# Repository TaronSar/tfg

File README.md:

# ProtoNet UAV — local few-shot identification prototype

Minimal local prototype of the TFG pipeline: MobileNetV3-Small -> 576 -> Linear ->
LayerNorm -> 128-dim L2-normalized embeddings, prototypical episodic training,
enrollment to `gallery.npy`, identification by cosine similarity. No Embention
infrastructure required — runs on a single PC (CUDA or CPU).

## Setup

```bash
python -m venv .venv && source .venv/bin/activate   # or conda
pip install -r requirements.txt
```

## Data layout

One folder per **physical airframe / distinct model**, split by identity
(an identity must never appear in both splits):

```
data/
  train/
    identity_A/ img001.jpg ...
    identity_B/ ...
  val/
    identity_X/ ...
```

Guideline: >=10 train identities and >=5 val identities, >=10 images each, to
see meaningful learning. Crops of the object (detector-style) work best, but
full photos are fine for a first smoke test.

## Test sequence

**0. Zero-shot sanity check (no training).** The ImageNet-pretrained encoder
already produces usable embeddings:

```bash
python -m src.enroll --images data/val/identity_X_subset5 --out gallery.npy
python -m src.identify --gallery gallery.npy --images data/val/identity_X_rest
python -m src.identify --gallery gallery.npy --images data/val/identity_Y   # impostor
```

If genuine scores already sit above impostor scores, the metric-learning
premise holds before you train anything.

**1. Train:**

```bash
python -m src.train --data_root ./data --epochs 30 \
    --n_way 5 --k_shot 5 --q_query 5 --degrade_p 0.5
```

`--degrade_p 0.5` randomly degrades training images to the 46–143 px
operational envelope (downscale + blur + upscale). Set `0` to disable —
comparing both runs is your first Q3 data point.

**2. Open-set evaluation (the number that matters):**

```bash
python -m src.eval_openset --checkpoint checkpoints/best.pth \
    --data_root ./data --k_shot 5 --agg mean
python -m src.eval_openset --checkpoint checkpoints/best.pth \
    --data_root ./data --k_shot 5 --agg attention   # Approach 2
```

Reports ROC-AUC (target vs impostor) and TPR at FPR 1/5/10%. Run with
`--checkpoint` omitted first to get the zero-shot baseline; training should
beat it clearly. Sweep `--k_shot 1 3 5 10` for an early Q1 curve.

**3. Manual enrollment demo (what the client-side app will do):**

```bash
python -m src.enroll --checkpoint checkpoints/best.pth \
    --images photos_of_target/ --out gallery.npy
python -m src.identify --checkpoint checkpoints/best.pth \
    --gallery gallery.npy --images query_crops/ --agg attention --threshold 0.6
```

## Distance metric (Snell et al. 2017)

The default metric is **squared Euclidean** (`--metric euclidean`), not cosine.
Squared Euclidean is a Bregman divergence, which is the property that makes the
class mean the optimal prototype. Cosine is kept as `--metric cosine` for the
ablation.

Subtlety specific to this project: the encoder L2-normalizes embeddings by
default (required by the gallery/threshold/privacy design). On the unit sphere,
squared Euclidean and cosine are monotonically equivalent, so the Bregman
justification is satisfied trivially. To reproduce the paper's *unnormalized*
Euclidean setting, train with `--no_l2norm` and compare — a legitimate ablation.

## Paper-aligned training options

- `--metric euclidean|cosine` — distance metric (default euclidean).
- `--no_l2norm` — disable final L2-normalization (unnormalized-Euclidean ablation).
- `--n_way` / `--test_n_way` — Snell et al. found training with **higher way**
  than test helps; set `--n_way` as high as your identity count allows and
  `--test_n_way` lower (e.g. train 15-way, test 5-way).
- `--k_shot_range 1 3 5 10` — sample shot per-episode to train a **shot-robust**
  model. The paper recommends matching train/test shot, but your test-time shot
  is the client's unknown N, so a single shot-robust model is the deployment-
  correct choice. Documented as a deliberate departure.
- `--paper_schedule` — reproduce their recipe: Adam, lr 1e-3, halved every
  2000 episodes, no weight decay, single LR for the whole network.

Note: the default (AdamW + cosine schedule + lower backbone LR + mild weight
decay) is tuned for fine-tuning a pretrained ImageNet backbone on few
identities — a different regime from the paper's from-scratch tiny conv nets.
Keep some weight decay: "BN is enough regularization" held at Omniglot scale,
not with a 2.5M-param backbone on tens of identities.

## Interpreting results

- **val acc (training log):** episodic 5-way accuracy on unseen identities.
  Chance = 0.20. Zero-shot ImageNet typically lands well above chance;
  training should push it substantially higher.
- **ROC-AUC (eval_openset):** 0.5 = useless, >0.9 = the approach works on
  your data. This is the go/no-go signal for the concept.
- **threshold:** take the threshold printed at your preferred FPR as the
  starting `--threshold` for identify.

## Files

- `src/model.py`     encoder (matches the TIDL split-export architecture) + prototype utils
- `src/dataset.py`   identity index, episodic sampler, operational degradation transform
- `src/train.py`     episodic training with identity-disjoint validation
- `src/enroll.py`    N images -> gallery.npy (Option A client-side artifact)
- `src/identify.py`  queries vs gallery, mean or attention aggregation
- `src/eval_openset.py`  ROC-AUC target-vs-impostor on held-out identities

## Notes

- Checkpoints store `embed_dim`/`image_size`; enroll/identify read them.
- The forward pass equals backbone_tidl.onnx + projection_head.onnx
  concatenated, so a trained `best.pth` exports through the existing split path.
- Training on an RTX 3090: a 30-epoch run at defaults is well under an hour.

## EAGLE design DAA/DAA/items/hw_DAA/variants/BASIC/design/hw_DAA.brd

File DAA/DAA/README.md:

# DAA

## Descripción

Documentacion de DAA.

## [VBN platform MVP](./docs/VBN/VBN_platform_MVP.md)

## [VBN platform v2]()

## [RadarAlt platform]()

## [Dev Environment](./docs/VBN/dev_environment.md)

## [Detection Model and AI Infrastructure](./items/sw/sw_daa/items/sw_ai/items/sw_ai_detection/docs/Entrenamiento_modelo.md)

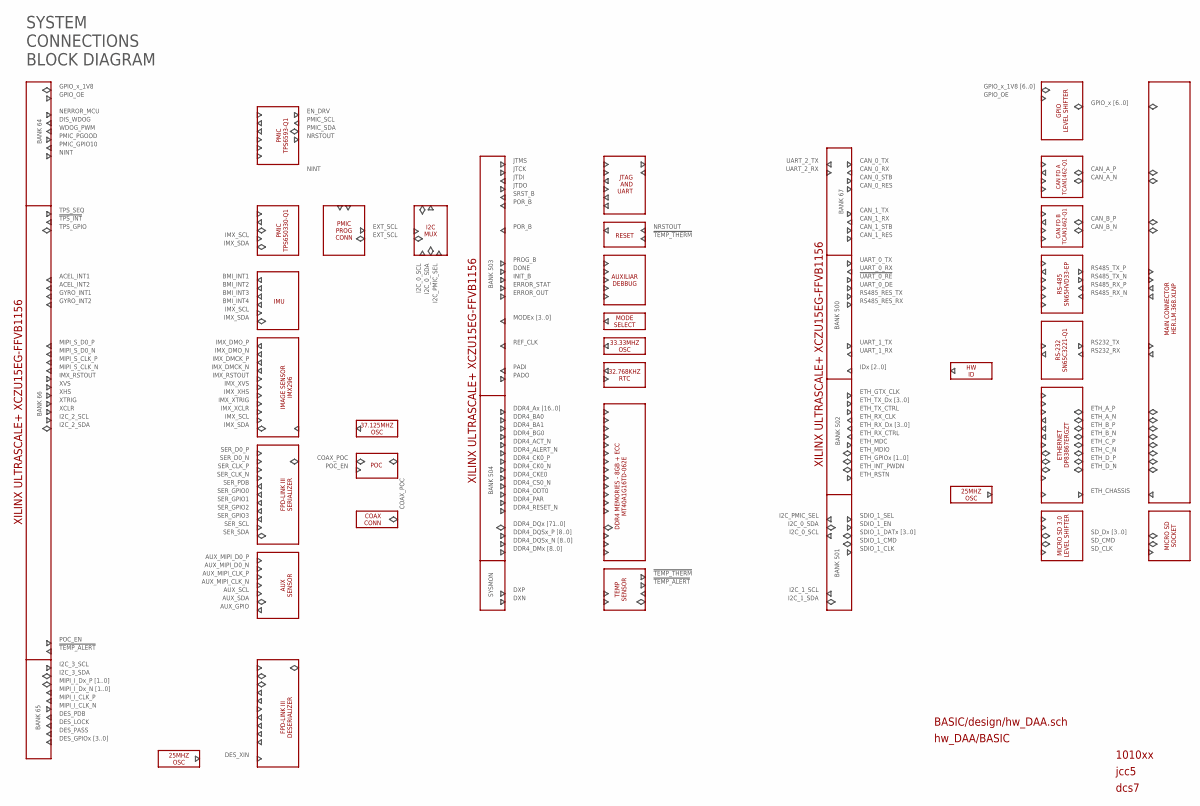
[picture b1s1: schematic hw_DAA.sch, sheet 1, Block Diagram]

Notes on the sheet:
XILINX ULTRASCALE+ XCZU15EG-FFVB1156
BANK 504
DDR4_DQx [71..0]
DDR4_DQSx_P [8..0]
DDR4_DQSx_N [8..0]
DDR4_DMx [8..0]
DDR4_Ax [16..0]
DDR4_BA0
DDR4_BA1
DDR4_BG0
DDR4_ACT_N
DDR4_ALERT_N
DDR4_CK0_P
DDR4_CK0_N
DDR4_CKE0
DDR4_CS0_N
DDR4_ODT0
DDR4_PAR
DDR4_RESET_N
JTMS
JTCK
DDR4 MEMORIES - 8GB + ECC MT40A1G16TD-062E
JTDI
JTDO
SRST_B
POR_B
DONE
INIT_B
ERROR_STAT
ERROR_OUT
MODEx [3..0]
PADI
PADO
REF_CLK
BANK 503
JTAG AND UART
MODE SELECT
33.33MHZ OSC
32.768KHZ RTC
SYSMON

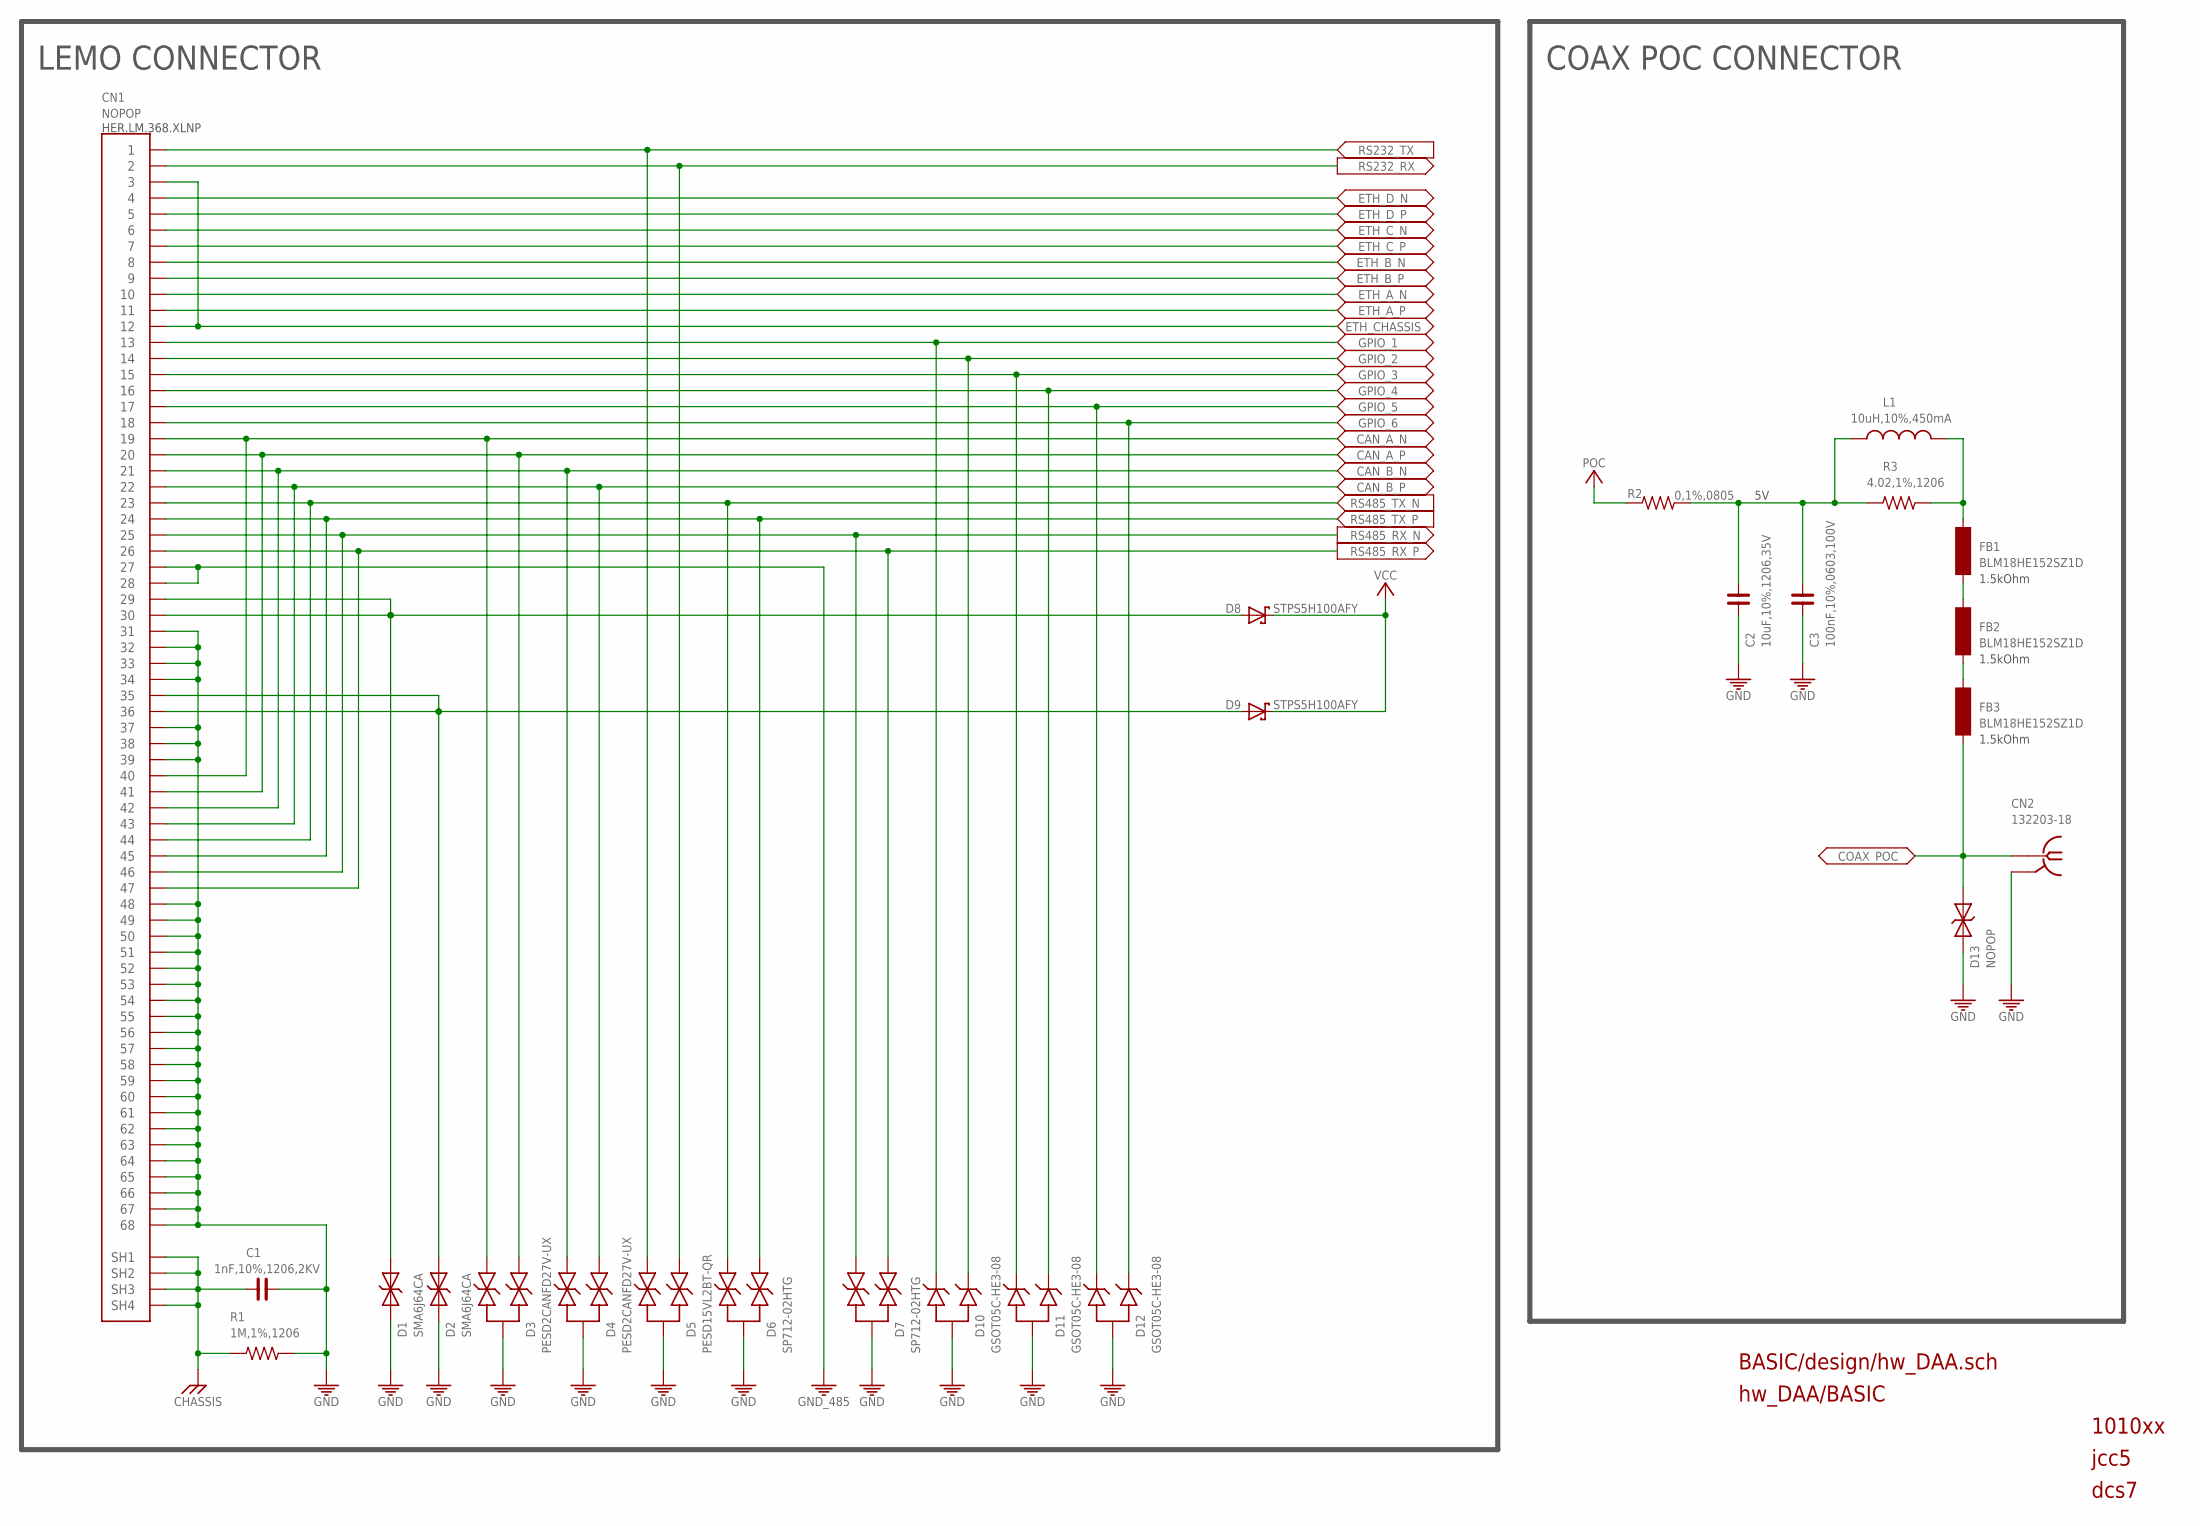
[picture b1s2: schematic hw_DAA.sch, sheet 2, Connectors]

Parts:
C1: 1nF,10%,1206,2KV; C1206
C2: 10uF,10%,1206,35V; C1206
C3: 100nF,10%,0603,100V; C0603
CN1: NOPOP; HEW.LM.368.XLNP
CN2: 132203-18
D1, D2: SMA6J64CA; SMA_BI
D3, D4: PESD2CANFD27V-UX; SOT323-3
D5: PESD15VL2BT-QR; SOT-23-3
D6, D7: SP712-02HTG; SOT-23-3
D8, D9: STPS5H100AFY; SOD128
D10, D11, D12: GSOT05C-HE3-08; SOT-23-3
D13: NOPOP; PESD0402-140
FB1, FB2, FB3: BLM18HE152SZ1D; L0603
L1: 10uH,10%,450mA; NLCV32T-100K-EFRD
R1: 1M,1%,1206; R1206
R2: 0,1%,0805; R0805
R3: 4.02,1%,1206; R1206

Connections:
CAN_A_N: CN1.19, CN1.40, D3.1; also elsewhere on the board
CAN_A_P: CN1.20, CN1.41, D3.2; also elsewhere on the board
CAN_B_N: CN1.21, CN1.42, D4.1; also elsewhere on the board
CAN_B_P: CN1.22, CN1.43, D4.2; also elsewhere on the board
CHASSIS: C1.1, CN1.SH1, CN1.SH2, CN1.SH3, CN1.SH4, R1.1; also elsewhere on the board
COAX_POC: CN2.RF, D13.P$2, FB3.1; also elsewhere on the board
ETH_A_N: CN1.10; also elsewhere on the board
ETH_A_P: CN1.11; also elsewhere on the board
ETH_B_N: CN1.8; also elsewhere on the board
ETH_B_P: CN1.9; also elsewhere on the board
ETH_CHASSIS: CN1.3, CN1.12; also elsewhere on the board
ETH_C_N: CN1.6; also elsewhere on the board
ETH_C_P: CN1.7; also elsewhere on the board
ETH_D_N: CN1.4; also elsewhere on the board
ETH_D_P: CN1.5; also elsewhere on the board
GND: C1.2, C2.1, C3.1, CN1.31, CN1.32, CN1.33, CN1.34, CN1.37, CN1.38, CN1.39, CN1.48, CN1.49, CN1.50, CN1.51, CN1.52, CN1.53, CN1.54, CN1.55, CN1.56, CN1.57, CN1.58, CN1.59, CN1.60, CN1.61, CN1.62, CN1.63, CN1.64, CN1.65, CN1.66, CN1.67, CN1.68, CN2.GND1 (GND), CN2.GND2 (GND), CN2.GND3 (GND), CN2.GND4 (GND), D1.1, D2.1, D3.3, D4.3, D5.3, D6.3, D7.3, D10.3, D11.3, D12.3, D13.P$1, R1.2; also elsewhere on the board
GND_485: CN1.27, CN1.28; also elsewhere on the board
GPIO_1: CN1.13, D10.1; also elsewhere on the board
GPIO_2: CN1.14, D10.2; also elsewhere on the board
GPIO_3: CN1.15, D11.1; also elsewhere on the board
GPIO_4: CN1.16, D11.2; also elsewhere on the board
GPIO_5: CN1.17, D12.1; also elsewhere on the board
GPIO_6: CN1.18, D12.2; also elsewhere on the board
unnamed: C2.2, C3.2, L1.1, R2.1, R3.1
unnamed: FB1.1, FB2.2
unnamed: FB1.2, L1.2, R3.2
unnamed: FB2.1, FB3.2
POC: R2.2; also elsewhere on the board
RS232_RX: CN1.2, D5.2; also elsewhere on the board
RS232_TX: CN1.1, D5.1; also elsewhere on the board
RS485_RX_N: CN1.25, CN1.46, D7.1; also elsewhere on the board
RS485_RX_P: CN1.26, CN1.47, D7.2; also elsewhere on the board
RS485_TX_N: CN1.23, CN1.44, D6.1; also elsewhere on the board
RS485_TX_P: CN1.24, CN1.45, D6.2; also elsewhere on the board
VCC: D8.K (C), D9.K (C); also elsewhere on the board
VIN_1: CN1.29, CN1.30, D1.2, D8.A
VIN_2: CN1.35, CN1.36, D2.2, D9.A

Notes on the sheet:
1010xx
jcc5
dcs7
LEMO CONNECTOR
COAX POC CONNECTOR
1.5kOhm
HER.LM.368.XLNP
BASIC/design/hw_DAA.sch
hw_DAA/BASIC

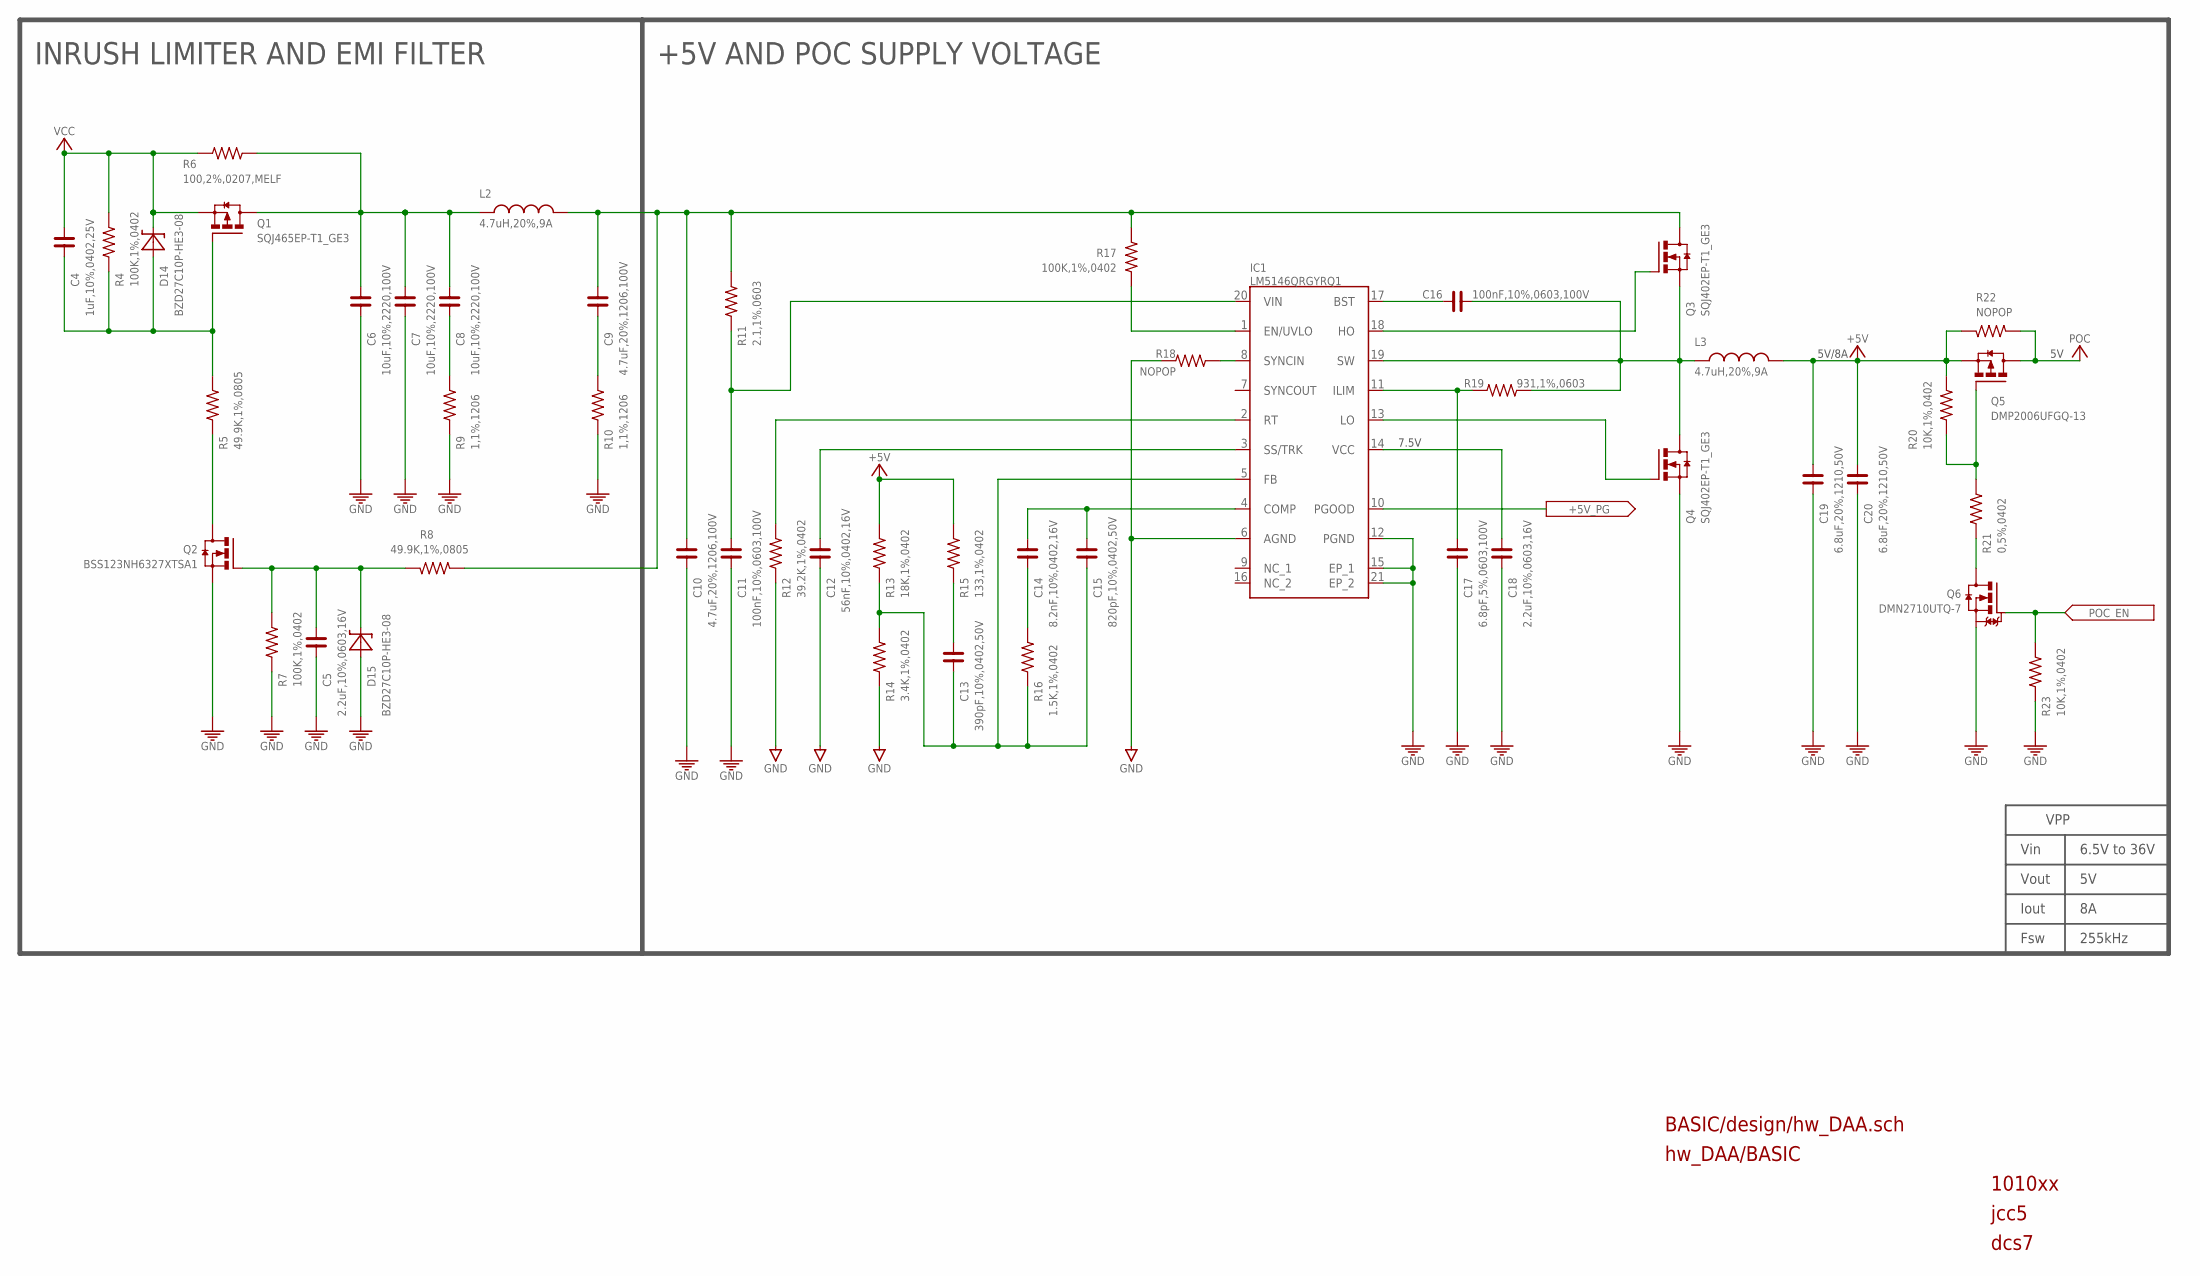
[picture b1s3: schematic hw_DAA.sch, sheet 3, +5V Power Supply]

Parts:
C4: 1uF,10%,0402,25V; C0402
C5, C18: 2.2uF,10%,0603,16V; C0603
C6, C7, C8: 10uF,10%,2220,100V; C2220K
C9, C10: 4.7uF,20%,1206,100V; C1206
C11, C16: 100nF,10%,0603,100V; C0603
C12: 56nF,10%,0402,16V; C0402
C13: 390pF,10%,0402,50V; C0402
C14: 8.2nF,10%,0402,16V; C0402
C15: 820pF,10%,0402,50V; C0402
C17: 6.8pF,5%,0603,100V; C0603
C19, C20: 6.8uF,20%,1210,50V; C1210
D14, D15: BZD27C10P-HE3-08; DO-219AB-2
IC1: LM5146QRGYRQ1; VQFN-20
L2, L3: 4.7uH,20%,9A; XAL7030-472
Q1: SQJ465EP-T1_GE3; SO-8L
Q2: BSS123NH6327XTSA1; SOT23-3
Q3, Q4: SQJ402EP-T1_GE3; SO-8L
Q5: DMP2006UFGQ-13; POWERDI3333-8
Q6: DMN2710UTQ-7; SOT-523
R4, R7, R17: 100K,1%,0402; R0402
R5, R8: 49.9K,1%,0805; R0805
R6: 100,2%,0207,MELF; MELF0207
R9, R10: 1,1%,1206; R1206
R11: 2.1,1%,0603; R0603
R12: 39.2K,1%,0402; R0402
R13: 18K,1%,0402; R0402
R14: 3.4K,1%,0402; R0402
R15: 133,1%,0402; R0402
R16: 1.5K,1%,0402; R0402
R18: NOPOP; R0402
R19: 931,1%,0603; R0603
R20, R23: 10K,1%,0402; R0402
R21: 0,5%,0402; R0402
R22: NOPOP; R0805

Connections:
+5V: C19.1, C20.1, L3.2, Q5.1 (S), Q5.2 (S), Q5.3 (S), R13.2, R15.2, R20.1, R22.1; also elsewhere on the board
+5V_PG: IC1.10 (PGOOD); also elsewhere on the board
GND: C5.2, C6.2, C7.2, C10.2, C11.2, C12.2, C17.2, C18.2, C19.2, C20.2, D15.A, IC1.6 (AGND), IC1.12 (PGND), IC1.15 (EP_1), IC1.21 (EP_2), Q2.2 (S), Q4.1 (S), Q4.2 (S), Q4.3 (S), Q6.2 (S), R7.2, R9.1, R10.1, R12.1, R14.1, R18.1, R23.2; also elsewhere on the board
HO: IC1.18 (HO), Q3.4 (G)
ILIM: C17.1, IC1.11 (ILIM), R19.2
LO: IC1.13 (LO), Q4.4 (G)
unnamed: Q5.4 (G), R20.2, R21.1
unnamed: IC1.2 (RT), R12.2
unnamed: C12.1, IC1.3 (SS/TRK)
unnamed: C13.2, C15.2, IC1.5 (FB), R13.1, R14.2, R16.1
unnamed: C14.2, R16.2
unnamed: C16.1, IC1.19 (SW), L3.1, Q3.1 (S), Q3.2 (S), Q3.3 (S), Q4.5 (D), Q4.EP1 (D), Q4.EP2 (D), R19.1
unnamed: C16.2, IC1.17 (BST)
unnamed: C9.1, C10.1, L2.2, Q3.5 (D), Q3.EP1 (D), Q3.EP2 (D), R8.1, R11.2, R17.2
unnamed: C8.2, R9.2
unnamed: C9.2, R10.2
unnamed: C18.1, IC1.14 (VCC)
unnamed: IC1.1 (EN/UVLO), R17.1
unnamed: IC1.8 (SYNCIN), R18.2
unnamed: C13.1, R15.1
unnamed: C11.1, IC1.20 (VIN), R11.1
unnamed: C4.2, D14.A, Q1.4 (G), R4.2, R5.1
unnamed: C6.1, C7.1, C8.1, L2.1, Q1.5 (D), Q1.EP1 (D), Q1.EP2 (D), R6.2
unnamed: C14.1, C15.1, IC1.4 (COMP)
unnamed: Q6.3 (D), R21.2
unnamed: Q2.3 (D), R5.2
unnamed: C5.1, D15.K (C), Q2.1 (G), R7.1, R8.2
POC: Q5.5 (D), Q5.6 (D), Q5.7 (D), Q5.8 (D), Q5.EP (D), R22.2; also elsewhere on the board
POC_EN: Q6.1 (G), R23.1; also elsewhere on the board
VCC: C4.1, D14.K (C), Q1.1 (S), Q1.2 (S), Q1.3 (S), R4.1, R6.1; also elsewhere on the board

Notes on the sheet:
1010xx
jcc5
dcs7
5V/8A
7.5V
INRUSH LIMITER AND EMI FILTER
+5V AND POC SUPPLY VOLTAGE
Vout
Iout
Fsw
Vin
6.5V to 36V
VPP
255kHz
BASIC/design/hw_DAA.sch
hw_DAA/BASIC

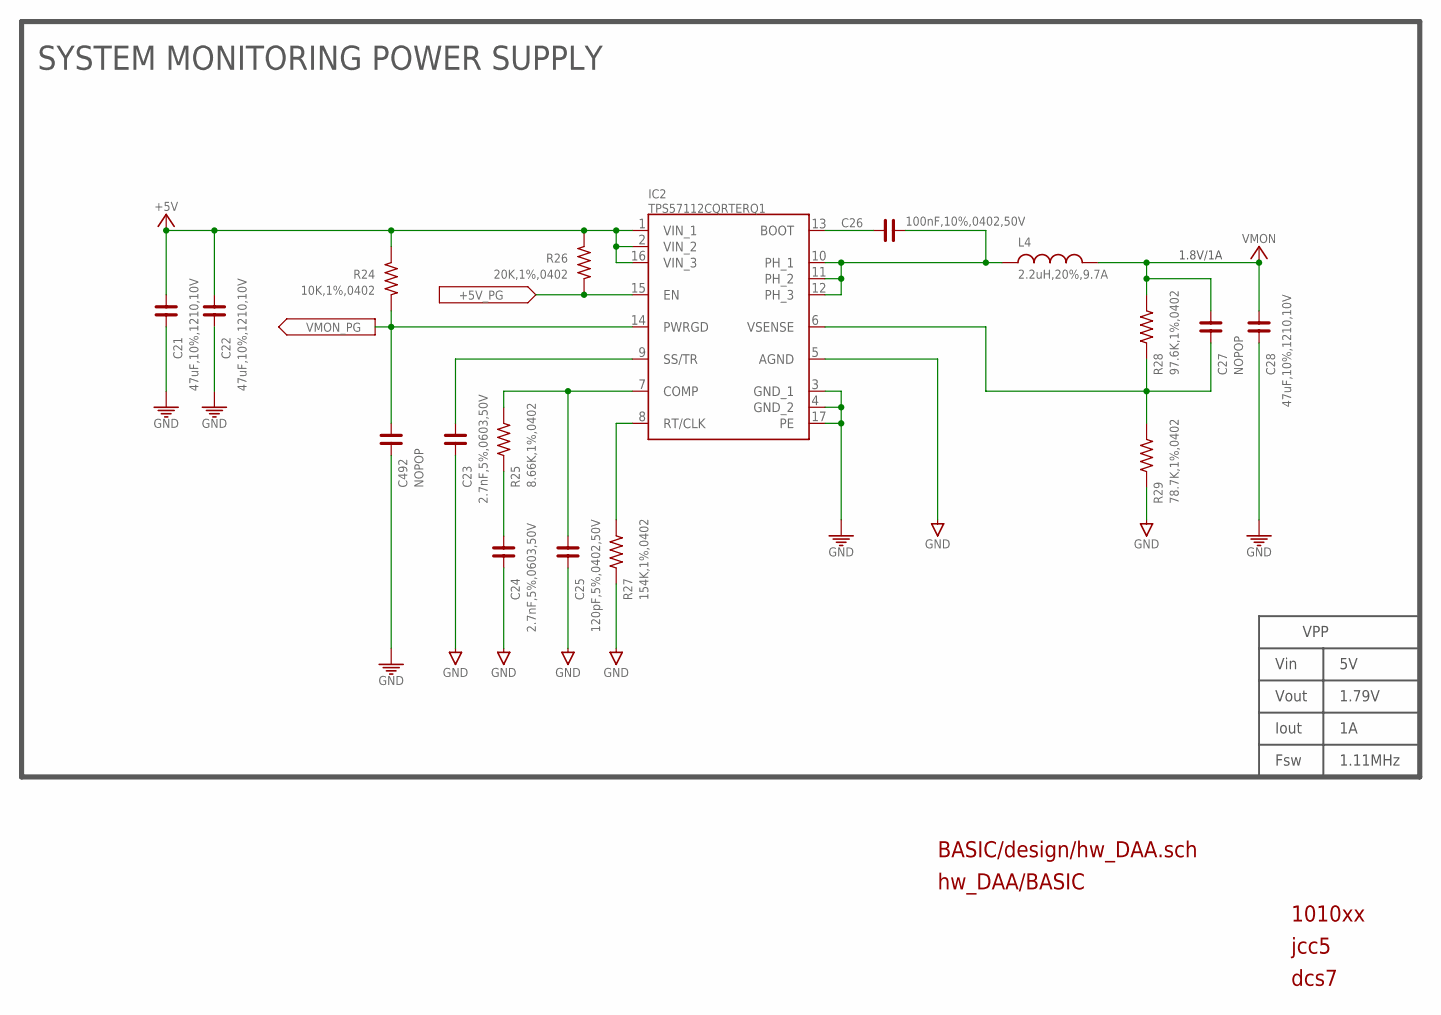
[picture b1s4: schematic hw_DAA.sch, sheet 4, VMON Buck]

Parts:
C21, C22, C28: 47uF,10%,1210,10V; C1210
C23, C24: 2.7nF,5%,0603,50V; C0603
C25: 120pF,5%,0402,50V; C0402
C26: 100nF,10%,0402,50V; C0402
C27, C492: NOPOP; C0402
IC2: TPS57112CQRTERQ1; WQFN-16
L4: 2.2uH,20%,9.7A; XAL50XX
R24: 10K,1%,0402; R0402
R25: 8.66K,1%,0402; R0402
R26: 20K,1%,0402; R0402
R27: 154K,1%,0402; R0402
R28: 97.6K,1%,0402; R0402
R29: 78.7K,1%,0402; R0402

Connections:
+5V: C21.1, C22.1, IC2.1 (VIN_1), IC2.2 (VIN_2), IC2.16 (VIN_3), R24.2, R26.2; also elsewhere on the board
+5V_PG: IC2.15 (EN), R26.1; also elsewhere on the board
GND: C21.2, C22.2, C23.2, C24.2, C25.2, C28.2, C492.2, IC2.3 (GND_1), IC2.4 (GND_2), IC2.5 (AGND), IC2.17 (PE), R27.1, R29.1; also elsewhere on the board
unnamed: C23.1, IC2.9 (SS/TR)
unnamed: C25.1, IC2.7 (COMP), R25.2
unnamed: C24.1, R25.1
unnamed: IC2.8 (RT/CLK), R27.2
unnamed: C27.2, IC2.6 (VSENSE), R28.1, R29.2
unnamed: C26.2, IC2.13 (BOOT)
unnamed: C26.1, IC2.10 (PH_1), IC2.11 (PH_2), IC2.12 (PH_3), L4.1
VMON: C27.1, C28.1, L4.2, R28.2; also elsewhere on the board
VMON_PG: C492.1, IC2.14 (PWRGD), R24.1; also elsewhere on the board

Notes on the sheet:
1010xx
jcc5
dcs7
1.8V/1A
Vout
Iout
Fsw
1.79V
Vin
VPP
1.11MHz
SYSTEM MONITORING POWER SUPPLY
BASIC/design/hw_DAA.sch
hw_DAA/BASIC

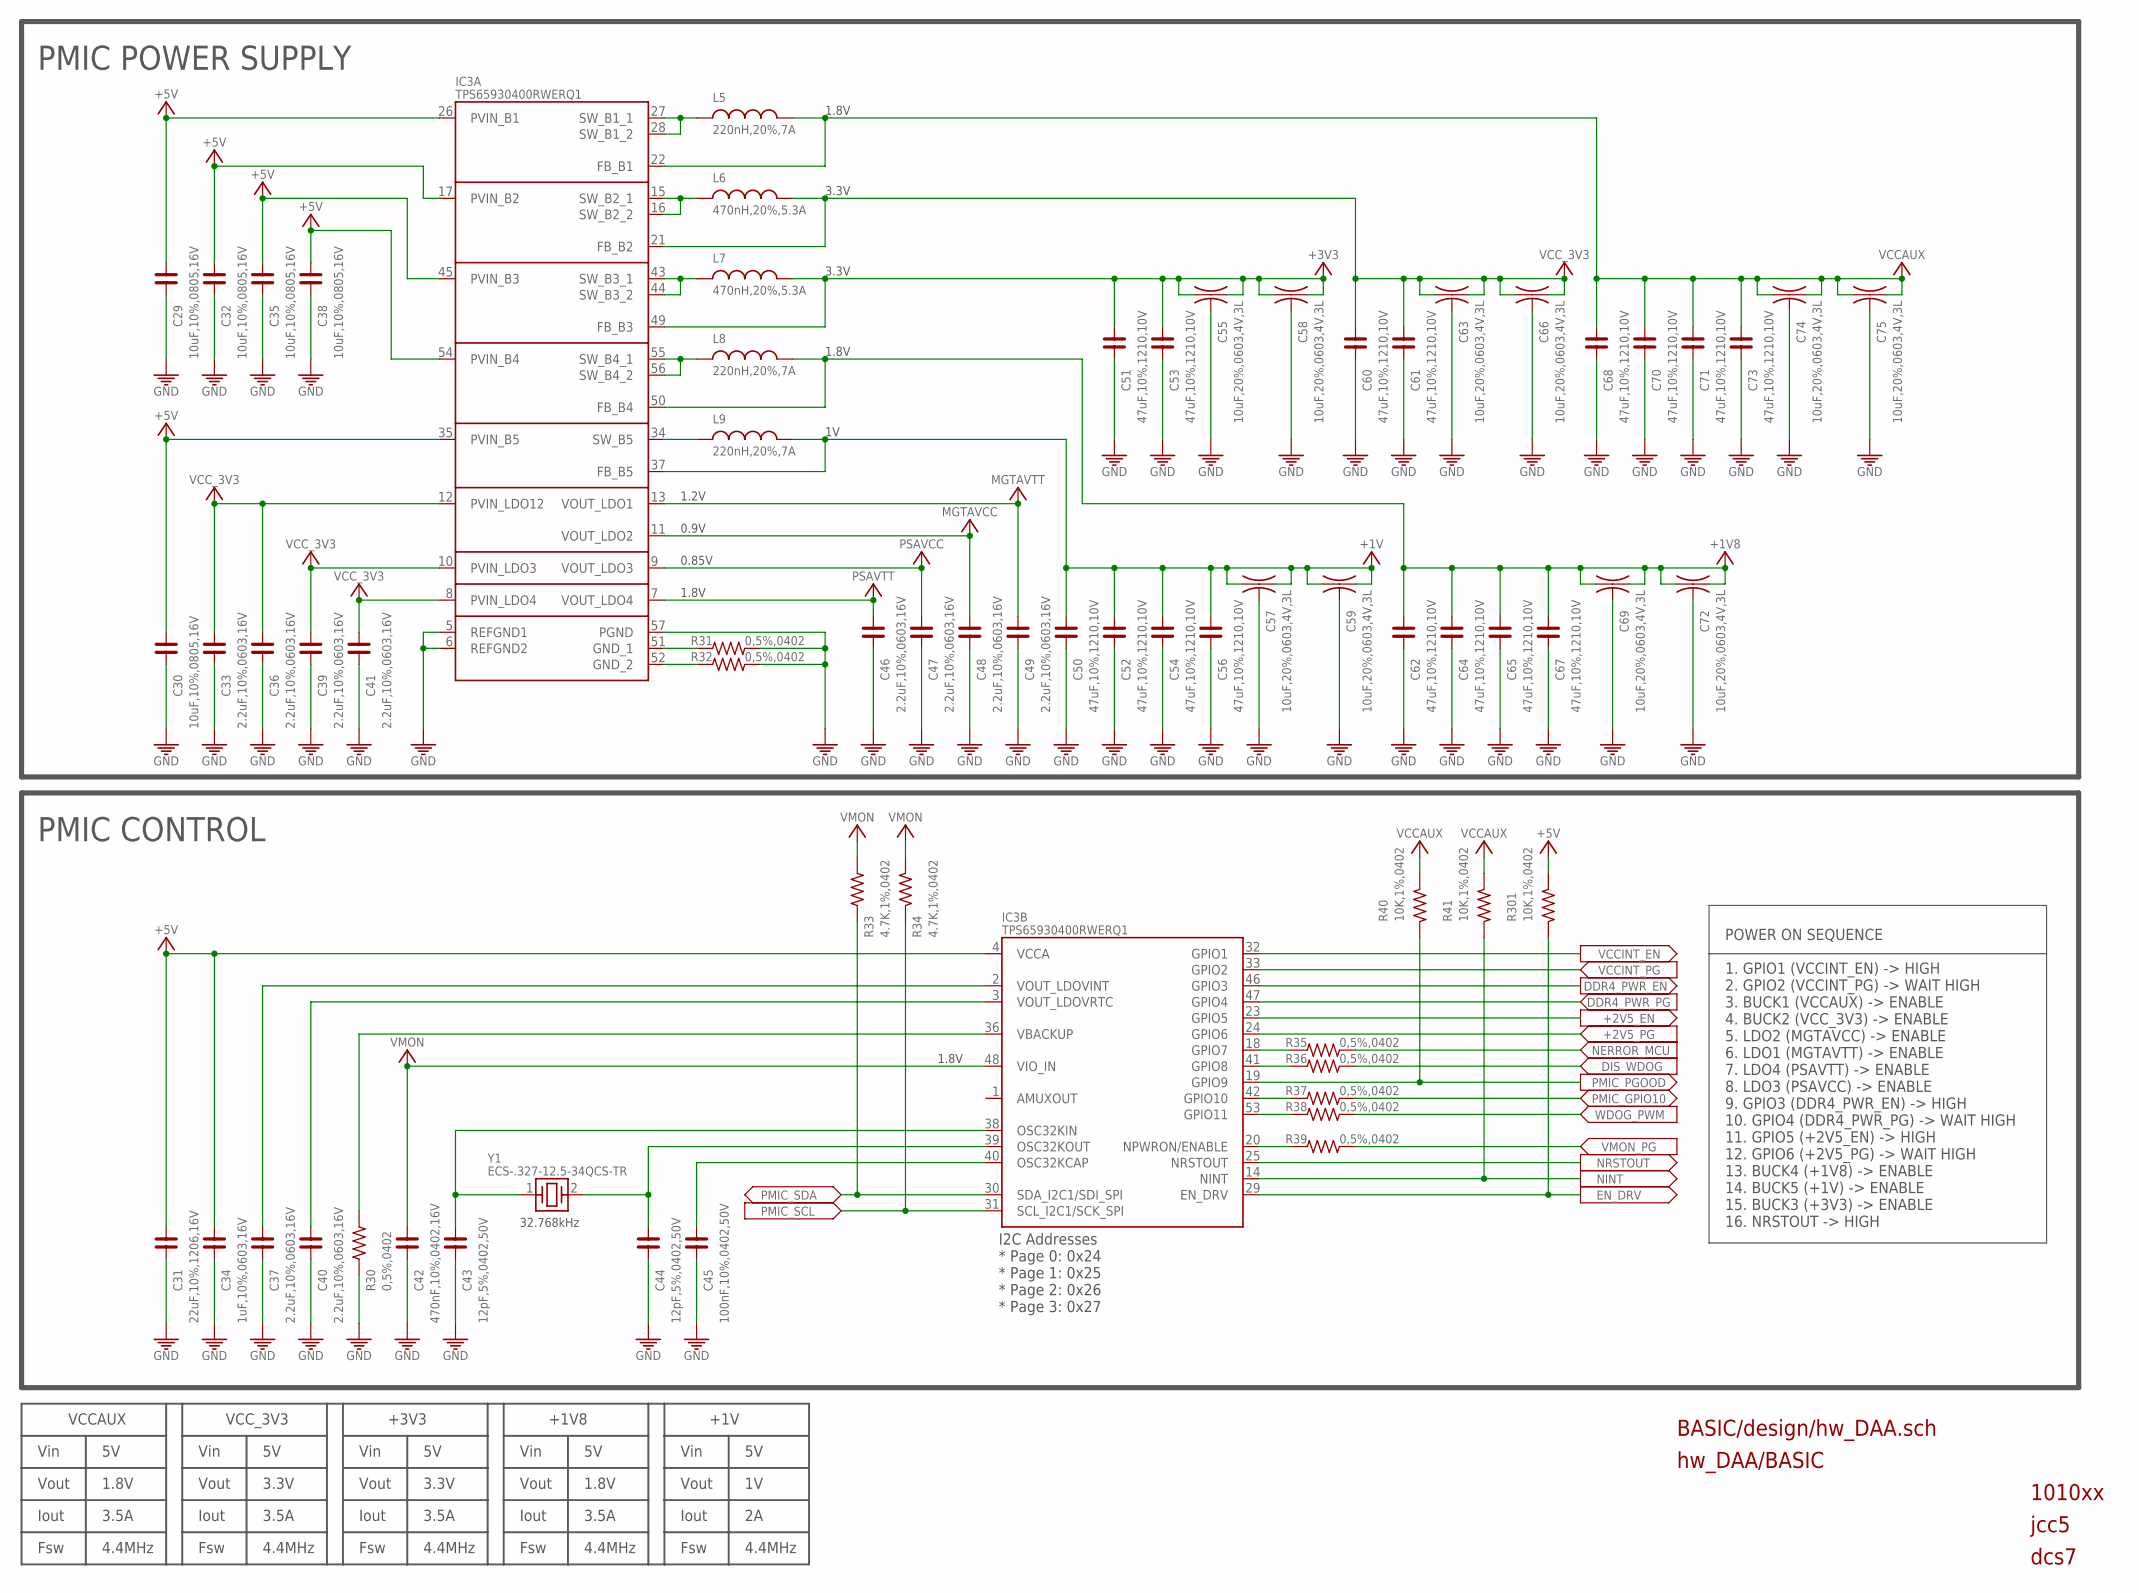
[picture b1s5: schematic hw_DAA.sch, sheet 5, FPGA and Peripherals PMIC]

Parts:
C29, C30, C32, C35, C38: 10uF,10%,0805,16V; C0805
C31: 22uF,10%,1206,16V; C1206
C33, C36, C37, C39, C40, C41, C46, C47, C48, C49: 2.2uF,10%,0603,16V; C0603
C34: 1uF,10%,0603,16V; C0603
C42: 470nF,10%,0402,16V; C0402
C43, C44: 12pF,5%,0402,50V; C0402
C45: 100nF,10%,0402,50V; C0402
C50, C51, C52, C53, C54, C56, C60, C61, C62, C64, C65, C67, C68, C70, C71, C73: 47uF,10%,1210,10V; C1210
C55, C57, C58, C59, C63, C66, C69, C72, C74, C75: 10uF,20%,0603,4V,3L; NFM18HC106
IC3: TPS65930400RWERQ1; VQFN-56
L5, L8, L9: 220nH,20%,7A; L1210
L6, L7: 470nH,20%,5.3A; L1210
R30, R31, R32, R35, R36, R37, R38, R39: 0,5%,0402; R0402
R33, R34: 4.7K,1%,0402; R0402
R40, R41, R301: 10K,1%,0402; R0402
Y1: ECS-.327-12.5-34QCS-TR; 3.2X1.5

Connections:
+1V: C50.1, C52.1, C54.1, C56.1, C57.1, C57.3, C59.1, C59.3, IC3.37 (FB_B5), L9.2; also elsewhere on the board
+1V8: C62.1, C64.1, C65.1, C67.1, C69.1, C69.3, C72.1, C72.3, IC3.50 (FB_B4), L8.2; also elsewhere on the board
+2V5_EN: IC3.23 (GPIO5); also elsewhere on the board
+2V5_PG: IC3.24 (GPIO6); also elsewhere on the board
+3V3: C51.1, C53.1, C55.1, C55.3, C58.1, C58.3, IC3.49 (FB_B3), L7.2; also elsewhere on the board
+5V: C29.1, C30.1, C31.1, C32.1, C34.1, C35.1, C38.1, IC3.4 (VCCA), IC3.17 (PVIN_B2), IC3.26 (PVIN_B1), IC3.35 (PVIN_B5), IC3.45 (PVIN_B3), IC3.54 (PVIN_B4), R301.1; also elsewhere on the board
DDR4_PWR_EN: IC3.46 (GPIO3); also elsewhere on the board
DDR4_PWR_PG: IC3.47 (GPIO4); also elsewhere on the board
DIS_WDOG: R36.2; also elsewhere on the board
EN_DRV: IC3.29 (EN_DRV), R301.2; also elsewhere on the board
GND: C29.2, C30.2, C31.2, C32.2, C33.2, C34.2, C35.2, C36.2, C37.2, C38.2, C39.2, C40.2, C41.2, C42.2, C43.2, C44.2, C45.2, C46.2, C47.2, C48.2, C49.2, C50.2, C51.2, C52.2, C53.2, C54.2, C55.2, C55.4 (2), C56.2, C57.2, C57.4 (2), C58.2, C58.4 (2), C59.2, C59.4 (2), C60.2, C61.2, C62.2, C63.2, C63.4 (2), C64.2, C65.2, C66.2, C66.4 (2), C67.2, C68.2, C69.2, C69.4 (2), C70.2, C71.2, C72.2, C72.4 (2), C73.2, C74.2, C74.4 (2), C75.2, C75.4 (2), IC3.5 (REFGND1), IC3.6 (REFGND2), IC3.57 (PGND), R30.1, R31.2, R32.2; also elsewhere on the board
MGTAVCC: C48.1, IC3.11 (VOUT_LDO2); also elsewhere on the board
MGTAVTT: C49.1, IC3.13 (VOUT_LDO1); also elsewhere on the board
unnamed: IC3.27 (SW_B1_1), IC3.28 (SW_B1_2), L5.1
unnamed: IC3.43 (SW_B3_1), IC3.44 (SW_B3_2), L7.1
unnamed: IC3.55 (SW_B4_1), IC3.56 (SW_B4_2), L8.1
unnamed: IC3.34 (SW_B5), L9.1
unnamed: IC3.15 (SW_B2_1), IC3.16 (SW_B2_2), L6.1
unnamed: IC3.51 (GND_1), R31.1
unnamed: IC3.52 (GND_2), R32.1
unnamed: IC3.53 (GPIO11), R38.1
unnamed: IC3.18 (GPIO7), R35.1
unnamed: IC3.41 (GPIO8), R36.1
unnamed: IC3.42 (GPIO10), R37.1
NERROR_MCU: R35.2; also elsewhere on the board
NINT: IC3.14 (NINT), R41.2; also elsewhere on the board
NPWRON/ENABLE1: IC3.20 (NPWRON/ENABLE), R39.1
NRSTOUT: IC3.25 (NRSTOUT); also elsewhere on the board
OSC32KCAP: C45.1, IC3.40 (OSC32KCAP)
OSC32KIN: C43.1, IC3.38 (OSC32KIN), Y1.1 (X1)
OSC32KOUT: C44.1, IC3.39 (OSC32KOUT), Y1.2 (X2)
PMIC_GPIO10: R37.2; also elsewhere on the board
PMIC_PGOOD: IC3.19 (GPIO9), R40.2; also elsewhere on the board
PMIC_SCL: IC3.31 (SCL_I2C1/SCK_SPI), R34.2; also elsewhere on the board
PMIC_SDA: IC3.30 (SDA_I2C1/SDI_SPI), R33.2; also elsewhere on the board
PSAVCC: C47.1, IC3.9 (VOUT_LDO3); also elsewhere on the board
PSAVTT: C46.1, IC3.7 (VOUT_LDO4); also elsewhere on the board
VBACKUP: IC3.36 (VBACKUP), R30.2
VCCAUX: C68.1, C70.1, C71.1, C73.1, C74.1, C74.3, C75.1, C75.3, IC3.22 (FB_B1), L5.2, R40.1, R41.1; also elsewhere on the board
VCCINT_EN: IC3.32 (GPIO1); also elsewhere on the board
VCCINT_PG: IC3.33 (GPIO2); also elsewhere on the board
VCC_3V3: C33.1, C36.1, C39.1, C41.1, C60.1, C61.1, C63.1, C63.3, C66.1, C66.3, IC3.8 (PVIN_LDO4), IC3.10 (PVIN_LDO3), IC3.12 (PVIN_LDO12), IC3.21 (FB_B2), L6.2; also elsewhere on the board
VMON: C42.1, IC3.48 (VIO_IN), R33.1, R34.1; also elsewhere on the board
VMON_PG: R39.2; also elsewhere on the board
VOUT_LDOVINT: C37.1, IC3.2 (VOUT_LDOVINT)
VOUT_LDOVRTC: C40.1, IC3.3 (VOUT_LDOVRTC)
WDOG_PWM: R38.2; also elsewhere on the board

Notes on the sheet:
1010xx
jcc5
dcs7
32.768kHz
1.8V
1.2V
0.9V
0.85V
PMIC POWER SUPPLY
PMIC CONTROL
POWER ON SEQUENCE 1. GPIO1 (VCCINT_EN) -> HIGH 2. GPIO2 (VCCINT_PG) -> WAIT HIGH 3. BUCK1 (VCCAUX) -> ENABLE 4. BUCK2 (VCC_3V3) -> ENABLE 5. LDO2 (MGTAVCC) -> ENABLE 6. LDO1 (MGTAVTT) -> ENABLE 7. LDO4 (PSAVTT) -> ENABLE 8. LDO3 (PSAVCC) -> ENABLE 9. GPIO3 (DDR4_PWR_EN) -> HIGH 10. GPIO4 (DDR4_PWR_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
Vout
Iout
Fsw
3.5A
4.4MHz
Vin
VCCAUX
3.3V
VCC_3V3
+3V3
+1V
+1V8
I2C Addresses * Page 0: 0x24 * Page 1: 0x25 * Page 2: 0x26 * Page 3: 0x27
BASIC/design/hw_DAA.sch
hw_DAA/BASIC

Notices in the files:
parts and their libraries:
COPYRIGHT: Copyright (C) 2023 Ultra Librarian. All rights reserved.
